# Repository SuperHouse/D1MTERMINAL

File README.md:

Terminal Shield for the WeMos D1 Mini
=====================================

Copyright 2016 SuperHouse Automation Pty Ltd  
SuperHouse site:  www.superhouse.tv  
SuperHouse email: info@superhouse.tv  

A general-purpose prototyping shield for the [WeMos D1 Mini][1] 
and other compatible boards based on the same header format,
with handy screw terminals for connecting external wires.

Features:

 * Screw terminals for all D1 Mini header pins.
 * Breakout pads for all D1 Mini header pins.
 * General purpose prototyping area for other parts.

More information is available at:

  http://www.superhouse.tv/d1mterminal

INSTALLATION
------------
The design is saved as an EAGLE project. EAGLE PCB design software is
available from www.cadsoftusa.com free for non-commercial use. To use
this project download it and place the directory containing these files
into the "eagle" directory on your computer.

DISTRIBUTION
------------
The specific terms of distribution of this project are governed by the
license referenced below.

LICENSE
-------
Licensed under the TAPR Open Hardware License (www.tapr.org/OHL).
The "license" folder within this repository also contains a copy of
this license in plain text format.

[1]: http://www.wemos.cc/wiki/doku.php?id=en:d1_mini

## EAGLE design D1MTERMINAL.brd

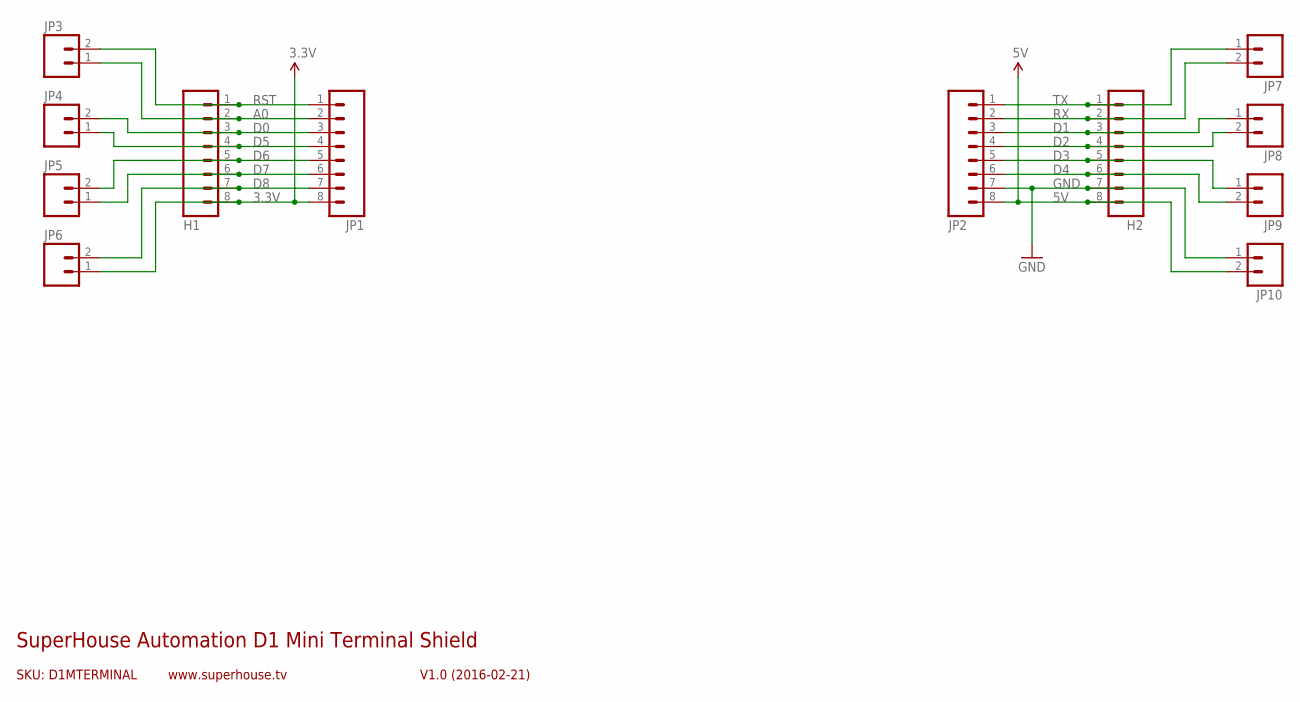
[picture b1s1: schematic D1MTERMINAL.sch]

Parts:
H1, H2: M08; 1X08
JP1, JP2: M08; 1X08
JP3, JP4, JP5, JP6, JP7, JP8, JP9, JP10: M023.5MM; SCREWTERMINAL-3.5MM-2

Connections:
3.3V: H1.8, JP1.8, JP6.1
5V: H2.8, JP2.8, JP10.2
A0: H1.2, JP1.2, JP3.1
D0: H1.3, JP1.3, JP4.2
D1: H2.3, JP2.3, JP8.1
D2: H2.4, JP2.4, JP8.2
D3: H2.5, JP2.5, JP9.1
D4: H2.6, JP2.6, JP9.2
D5: H1.4, JP1.4, JP4.1
D6: H1.5, JP1.5, JP5.2
D7: H1.6, JP1.6, JP5.1
D8: H1.7, JP1.7, JP6.2
GND: H2.7, JP2.7, JP10.1
RST: H1.1, JP1.1, JP3.2
RX: H2.2, JP2.2, JP7.2
TX: H2.1, JP2.1, JP7.1

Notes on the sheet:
SKU: D1MTERMINAL
SuperHouse Automation D1 Mini Terminal Shield
V1.0 (2016-02-21)
www.superhouse.tv

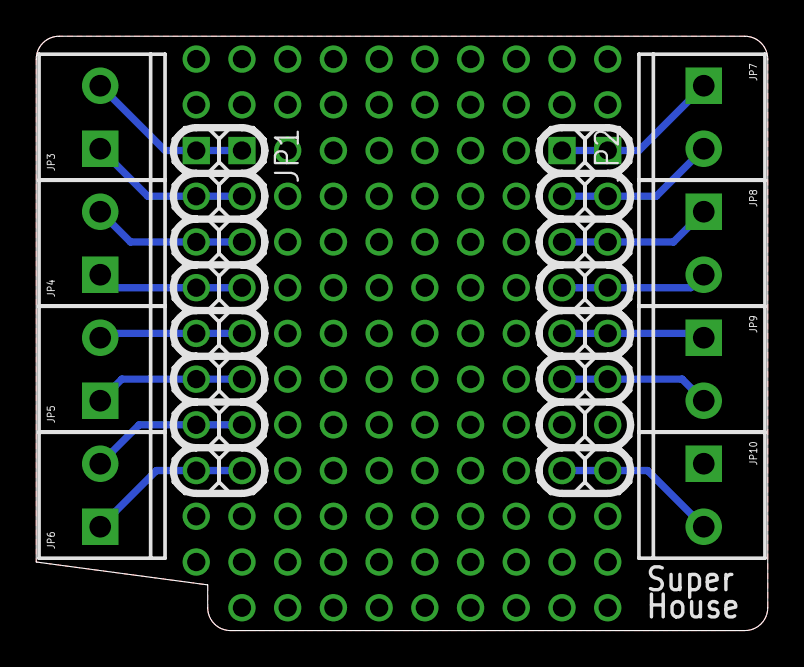
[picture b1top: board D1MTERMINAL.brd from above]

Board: 2 copper layers, 40.6 x 33.0 mm, 12 parts (0 on the bottom side), 16 nets.

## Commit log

2016-02-26 Initial import
2016-02-26 Added licence information and updated README
2016-02-26 Added preview images
2016-02-26 Added more preview images to README
2016-02-26 Fixed syntax error
2016-02-26 Clarified description
2017-10-31 Fixed annular rings on proto area. Maybe! Need to check gerbers
2017-10-31 Added image of dodgy prototype with silkscreen over proto area

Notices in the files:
parts and their libraries:
freetronics-original: Licensing: CC v3.0 Share-Alike You are welcome to use this library for commercial purposes.
